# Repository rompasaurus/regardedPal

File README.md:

# Dilder

A Tamagotchi-inspired virtual pet built on a Raspberry Pi Pico W with an e-ink display, battery pack, and 3D-printed case — developed entirely in the open as a learning platform, blog series, and YouTube companion project.

The goal isn't just to build a thing — it's to show *how* the thing gets built, from the very first idea to a finished handheld device. Every prompt, every design decision, every dead end is documented so anyone can follow along, learn, and build their own.

---

## How It Started — Meet Jamal

<p align="center">
  
  <br />
  <em>Jamal. The plush octopus who started it all.</em>
</p>

This project didn't start with a schematic or a product spec. It started in a TEDi — a German dollar store — where my wife Emma and I found a giant plush octopus grinning up from a discount bin. We bought him on the spot, and on the walk home we started giving him a personality: laid-back, opinionated, a little sassy, suspiciously wise for a boneless creature. By the time we got home, he had a name — **Jamal** — and he'd claimed the armchair like he'd been paying rent.

The question asked itself: *what if we could actually bring him to life?* Not literally — but as a tiny digital companion. A pocket-sized octopus with moods, opinions, and an attitude problem, living on an e-ink screen and judging your life choices in ALL CAPS.

That's how Dilder was born. Not from an engineering roadmap, but from a stuffed animal and two people who couldn't stop anthropomorphizing it on a walk home.

---

## Enclosure — Rev 2 Mk2

The 3D-printed enclosure is a three-part design: base plate with solar panel recess, AAA battery cradle insert, and top cover with display window and joystick cutout. Designed in OpenSCAD (parametric source) and FreeCAD (visual PartDesign).

### Individual Parts

<p align="center">
  <em>Left: Base plate with cradle pocket, corner pillars, battery rail troughs, and USB-C cutout. Right: AAA battery cradle with dual bays, clip slots, and TP4056 indent.</em>
</p>

<p align="center">
  <em>Left: Top cover with display window, joystick hole, and bullnose edge. Right: Base plate bottom showing solar panel recess and wire holes.</em>
</p>

### Assembled

<p align="center">
  
  <br />
  <em>All three parts stacked in their mated positions.</em>
</p>

### Full Assembly with Electronics

The FreeCAD macro now imports the official Raspberry Pi Pico 2 STEP file (mechanically identical to the Pico 2 W) and adds procedural 2×20 pin headers. It also builds three more peripherals from datasheet dimensions — two AAA Li-Ion cells in the cradle bays, a TP4056 USB-C charge module in the connecting block indent, and a Waveshare 2.13" e-paper display in the top cover's screen inlay. The Pico is mounted upside-down with its component-side face flush against the cradle's mating plane, headers extending up into the PicoNest cavity.

<p align="center">
  
  <br />
  <em>Top cover rendered translucent so the Pico 2 W board, headers, and cradle are all visible.</em>
</p>

<p align="center">
  <em>Left: top cover hidden so the cradle and Pico are exposed. Right: cradle hidden so the Pico's seating on the base plate is visible — header pin tips reach the level where the cradle would clip in.</em>
</p>

See the [FreeCAD macro reference](website/docs/docs/hardware/freecad-mk2-macro.md) for a full walkthrough of how the macro is structured.

### Joystick Thumbpiece

A printable snap cap that fits over the K1-1506SN-01 5-way switch peg. Single disc, 11 mm OD (= cover hole − 1 mm) so it nests inside the cover's joystick cutout with 0.5 mm radial clearance for directional swing. Concave thumb dish on top, rectangular snap socket on the bottom centered on the actuator (the SW1 stick is offset +0.68 mm in Y from the cover hole on the production PCB layout — disc reads visually centered, socket lands on the peg). Built parametrically in `dilder_rev2_mk2.FCMacro` as a separate `Thumbpiece` Body — drop `thumb_sock_x/y` from 3.3 to ~3.15 in the spreadsheet to convert friction-fit to interference snap-fit.

<p align="center">
  
  <br />
  <em>Top-down view of the assembled prototype — display window on the left, joystick with the new thumbpiece on the right.</em>
</p>

<p align="center">
  <em>Left: joystick area in context. Right: thumbpiece nested in the cover cutout with the cover dialed to 85% transparency for clarity.</em>
</p>

See the [thumbpiece design write-up](website/docs/blog/posts/joystick-thumbpiece-snap-cap.md) for the geometry walkthrough — including the dish-vs-socket constraint that almost ruined the first cut.

---

## What This Project Is

- **A virtual pet device** — a pocket-sized, low-power companion with personality, needs, and interactions displayed on an e-ink screen
- **A build series** — a step-by-step guide covering hardware, software, 3D printing, and project planning
- **A transparency experiment** — the entire development process is captured in real time, including AI-assisted prompts, iteration, and mistakes

---

## Hardware

### Phase 1 — Pico W Prototype (current)

| Component | Details |
|-----------|---------|
| Board | Raspberry Pi Pico W (or Pico WH with pre-soldered headers) |
| Display | [Waveshare Pico-ePaper-2.13](https://www.waveshare.com/pico-epaper-2.13.htm) — 250x122px, black & white, SPI1, SSD1680 driver, Pico-native 40-pin plug-in module |
| Power | USB micro-B (development); battery TBD |
| Input | 5x 6x6mm tactile push buttons (3 nav + 2 action) via GPIO |

### Future — Pi Zero Upgrade

| Component | Details |
|-----------|---------|
| Board | Raspberry Pi Zero WH (W or 2 W, pre-soldered headers) |
| Power | LiPo battery + Adafruit PowerBoost 500C |
| Enclosure | 3D-printed case (STL files provided) |

> The Pico W is the starting platform — it's what we have on hand, it's cheap, and it's excellent for prototyping the display and input system. The Pi Zero upgrade comes later when we need Linux, networking features, or more compute.

---

## Phases

Each phase maps to a section of the blog/YouTube series and can be followed independently.

### Phase 0 — Project Planning & Documentation ✓

- [x] Create repository and project structure
- [x] Define project intent and scope
- [x] Begin prompt progression log ([PromptProgression.md](PromptProgression.md))
- [x] Outline full phase roadmap
- [x] Create pixel art concepts for e-ink display (octopus character with 16 emotional states)
- [x] Define enclosure concept and prototype dimensions

### Phase 1 — Hardware Selection & Setup (Pico W) ✓

- [x] Finalize component list with links/part numbers ([hardware-research.md](docs/hardware-research.md))
- [x] Set up Docker-based C SDK cross-compilation toolchain
- [x] Wire e-ink display to Pico W via jumper wires (SPI)
- [x] Flash and run "Hello, Dilder!" on the e-ink display — proof of life
- [x] Build DevTool GUI — display emulator, serial monitor, firmware flash, asset manager, GPIO reference, connection utility, documentation ([tools/devtool/](tools/devtool/))
- [x] Add Programs tab with animated octopus preview, firmware size estimation, and deploy
- [x] Build IMG-receiver firmware — stream images from PC to Pico display via USB serial ([dev-setup/img-receiver/](dev-setup/img-receiver/))
- [x] Build standalone deploy — runtime-rendered animation, runs without PC
- [ ] Wire and test button inputs (GPIO)
- [ ] Battery power prototype

### Phase 2 — Firmware Foundation (C on Pico W)
> *You are here*

- [x] Runtime rendering engine — draw octopus mathematically (no pre-baked frames)
- [x] Animation system — 4-frame mouth cycle with per-mood expression sequences
- [x] Body transform system — dx/dy offset, x_expand, per-row sine wobble
- [x] Custom body shapes for Fat (wider dome, thick tentacles) and Lazy (tentacles draped right)
- [x] 16 emotional states with unique eyes, pupils, eyebrows, eyelids, mouths, and body animations
- [x] 17 standalone firmware programs (16 emotions + mood selector with all 823 quotes)
- [x] Date/time clock header from RTC
- [x] C-faithful preview renderer for verifying firmware matches DevTool
- [x] Keyboard-to-Pico input mapping plan ([docs/keyboard-to-pico-input.md](docs/keyboard-to-pico-input.md))
- [x] Implement serial command input for interactive mood control
- [x] Wire and test GPIO joystick input (DollaTek 5-way, GP2–GP6)
- [x] Joystick Mood Selector firmware with on-screen input indicator
- [ ] **Custom PCB design (in progress)** — switched MCU from RP2040 to ESP32-S3-WROOM-1-N16R8 (WiFi+BLE, 16MB flash, 8MB PSRAM). 4-layer board (45x80mm, 30 components) in KiCad, ready for routing. Target fab: JLCPCB. Sensors: LIS2DH12TR (accelerometer), AHT20 (temperature/humidity), BH1750FVI-TR (ambient light) on shared I2C bus.
- [ ] Battery power (LiPo on VSYS) — InnCraft 1000mAh acquired
- [ ] Build game loop with state machine (idle, interact, sleep)

### Phase 3 — Pet Logic & Gameplay

- [ ] Define pet stats (hunger, happiness, energy, health, etc.)
- [ ] Implement stat decay over time
- [ ] Build interaction system — feed, play, sleep, clean
- [x] Pet mood / expressions based on emotional states (16 implemented)
- [x] Animation frames for e-ink (idle expressions, body movement per mood)
- [ ] Emotional state transitions triggered by interactions and stats
- [ ] Add death/game-over state and reset/new-pet flow

### Phase 4 — UI & Menus

- [ ] Design menu system for e-ink (optimized for minimal refreshes)
- [ ] Build status bar — icons for stats, clock, battery level
- [ ] Add screen transitions between menu, pet view, and interactions
- [ ] Implement settings screen (contrast, name pet, reset)

### Phase 5 — Pi Zero Migration

- [ ] Port MicroPython firmware to CPython on Pi Zero
- [ ] Set up headless Raspberry Pi OS
- [ ] Adapt display driver for Pi Zero SPI + Waveshare HAT
- [ ] Adapt input handler for Pi Zero GPIO
- [ ] Validate all Phase 2-4 functionality on Pi Zero

### Phase 6 — 3D-Printed Case & Power
> *In progress alongside Phase 2*

- [x] Design enclosure in OpenSCAD — parametric 3-part design (base plate, AAA cradle, top cover)
- [x] Account for display cutout, joystick access, USB-C charging port, solar panel recess
- [x] Translate to FreeCAD PartDesign — full parametric model with 90+ parameter spreadsheet
- [x] Battery cradle with clip slots for Swpeet AAA contact plates (parallel wiring)
- [x] Solar panel wire through-holes in base plate
- [x] Print prototypes and iterate on fit (Rev 2 Mk2 current)
- [ ] Implement battery power (dual 10440 or single 3000mAh LiPo via TP4056)
- [ ] Implement sleep/wake cycle to conserve battery
- [x] Publish STL/3MF files and build instructions ([hardware-design/freecad-mk2/](hardware-design/freecad-mk2/))

### Phase 7 — Extras & Community

- [ ] Add sound (piezo buzzer for beeps/alerts)
- [ ] Explore connectivity — Bluetooth/Wi-Fi pet interactions?
- [ ] Mini-games
- [ ] Seasonal/event-based pet outfits or moods
- [ ] Publish a "build your own" kit guide
- [ ] Community gallery — show off your Dilder

---

## Content & Documentation

| Resource | Description |
|----------|-------------|
| [PromptProgression.md](PromptProgression.md) | Every AI prompt used in development (104+), timestamped with token counts and file changes |
| [docs/hardware-research.md](docs/hardware-research.md) | Component research, materials list, GPIO pinout, and enclosure concepts |
| [Emotion States](https://dilder.dev/docs/software/emotion-states/) | All 16 emotional states with rendered previews and animation strips |
| [docs/keyboard-to-pico-input.md](docs/keyboard-to-pico-input.md) | Input mapping plan for interactive octopus control |
| [Blog](https://dilder.dev/blog/) | Build journal — 8 posts covering planning through body animations |
| YouTube (TBD) | Video walkthroughs for each phase |

---

## Follow Along

This project is built in the open. Star/watch this repo to follow progress. Each phase will have a corresponding blog post and video.

---

## License

TBD

---

*Built with patience, a Pico W, and an unreasonable fondness for a plush octopus named Jamal.*

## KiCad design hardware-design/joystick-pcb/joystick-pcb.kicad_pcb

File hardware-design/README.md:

# Build & Render Tool

Interactive CLI pipeline for rendering Dilder FreeCAD models into publication-quality PNGs.

## Quick Start

```bash
cd hardware-design
./build_and_render.sh
```

## What It Does

1. **Pick a model** — interactive menu lists all `.FCStd` files sorted by date (newest first)
2. **Choose what to render** — 19 options from full sets to individual components
3. **Set render style** — resolution, background, cover transparency
4. **Renders** — launches FreeCAD GUI, generates PNGs from the live 3D viewport
5. **Copies to website** — drops renders into `website/docs/assets/images/enclosure/`

## Menu Options

### Full Sets
| Option | Description | Images |
|--------|-------------|--------|
| 1 | Everything | 40+ |
| 2 | Assembly only | 10 |
| 3 | Exploded views | 3 |
| 4 | Component portraits | 14 |

### Individual Bodies
| Option | Description |
|--------|-------------|
| 5 | Base plate (iso + top + bottom + sensors) |
| 6 | AAA cradle (iso + top + bottom) |
| 7 | Top cover (transparent + opaque + bottom) |
| 8 | Thumbpiece |

### Peripherals
| Option | Description |
|--------|-------------|
| 9 | Joystick PCB (K1-1506SN-01 breakout) |
| 10 | Pico 2 W + headers |
| 11 | Piezo speaker (20 mm FT-20T) |
| 12 | IMU accelerometer (GY-6500) |
| 13 | TP4056 charger |
| 14 | Batteries + clips |
| 15 | E-ink display |
| 16 | Solar panel |

### Special
| Option | Description |
|--------|-------------|
| 17 | Detail close-ups (joystick, thumbpiece, sensors) |
| 18 | Animation frames (13-step assembly drop) |
| 19 | Custom combo (pick exactly which components) |

## Render Styles

- **Resolution:** 1920x1440 (default), 2560x1920, 1280x960, 960x720
- **Background:** Transparent (default), White, Black, Light gray
- **Cover transparency:** 40% (default), 0% (opaque), 70%, 85% (ghost)

## Animation

Option 18 generates frame-by-frame PNGs of components dropping into place with cosine ease-in-out. If `ffmpeg` is installed, assembles them into a GIF automatically.

```bash
# Manual GIF assembly if needed
ffmpeg -framerate 12 -i renders/anim/frame-%04d.png \
       -vf "scale=960:720" -loop 0 renders/assembly-animation.gif
```

## Flags

```bash
./build_and_render.sh --rebuild    # rebuild FCStd from macro before rendering
./build_and_render.sh --all        # (with animation) not needed — pick option 18 in menu
```

## Output

- `renders/var-*.png` — assembly views (hero, angles, exploded, etc.)
- `renders/comp-*.png` — isolated component portraits
- `renders/anim/frame-*.png` — animation frames
- Automatically copied to `website/docs/assets/images/enclosure/`

## Requirements

- FreeCAD (GUI version, not `freecadcmd` — needs the 3D viewport for `saveImage`)
- `ffmpeg` (optional, for GIF assembly)
- `identify` from ImageMagick (optional, for blank image detection)

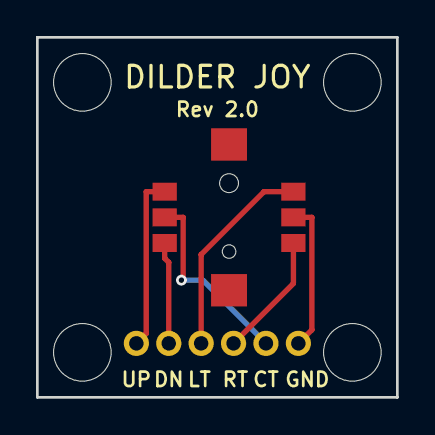
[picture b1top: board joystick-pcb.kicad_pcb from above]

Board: 2 copper layers, 20.0 x 20.0 mm, 6 parts (0 on the bottom side), 6 nets.

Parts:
H1, H2, H3, H4: M3; MountingHole_3.2mm_M3
J1: Wire_Pads; WirePads_1x06_P1.8mm
SW1: SKRHABE010

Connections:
GND: J1.6, SW1.5
JOY_CENTER: J1.5, SW1.2
JOY_DOWN: J1.2, SW1.3
JOY_LEFT: J1.3, SW1.4
JOY_RIGHT: J1.4, SW1.6
JOY_UP: J1.1, SW1.1

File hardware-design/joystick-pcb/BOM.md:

# Dilder Joystick Breakout PCB — Bill of Materials

## Rev 1.0 — 2026-04-25

---

### Components

| Ref | Qty | Description | Manufacturer | MPN | LCSC / JLCPCB | Package | Unit Price | Notes |
|-----|-----|-------------|-------------|-----|---------------|---------|------------|-------|
| SW1 | 1 | 5-direction SMD navigation switch | Alps Alpine | SKRHABE010 | C139794 | SMD-8P, 7.5x7.5mm | $0.50 (qty 100) | Primary joystick input |
| J1 | 1 | 1x6 through-hole wire pads | — | — | — | 2.0mm pitch, PTH | $0.00 | Bare pads for hand-soldered wires |
| H1-H4 | 4 | M3 mounting hole | — | — | — | 3.2mm drill, NPTH | $0.00 | Board-only (no BOM part) |

### PCB Fabrication

| Parameter | Value |
|-----------|-------|
| Board size | 20 x 20 mm |
| Layers | 2 (F.Cu + B.Cu) |
| Thickness | 1.0 mm |
| Copper weight | 1 oz |
| Surface finish | HASL (lead-free) |
| Solder mask | Green (default) |
| Silkscreen | White |
| Min trace width | 0.3 mm |
| Min drill | 1.0 mm (wire pads) |
| NPTH drills | 3.2 mm x4 (M3 mounting) |

### JLCPCB Order Notes

- **PCB only (no assembly):** Order 5-10 boards at ~$2 for the lot
- **With PCBA (recommended):** Use Economic PCBA, single-side SMT
  - SKRHABE010 is an **Extended Part** — $3 setup fee per unique extended part
  - Assembly requires fixture (noted on JLCPCB part page)
  - Upload BOM CSV + CPL (pick-and-place) file
  - J1 wire pads are hand-soldered after assembly — exclude from PCBA BOM

### Alternative Components (drop-in replacements)

| MPN | Manufacturer | LCSC | Price | Stock | Notes |
|-----|-------------|------|-------|-------|-------|
| SKRHABE010 | Alps Alpine | C139794 | $0.50 | ~3,325 | **Primary choice** |
| TM-4175-B-A | XKB Connection | C465995 | $0.73 | ~748 | Same 8-pin footprint, compatible |
| SKRHADE010 | Alps Alpine | C202415 | $0.85 | ~742 | Alps variant, same footprint |

### Wiring to ESP32-S3 (Olimex DevKit-Lipo)

| J1 Pin | Signal | Wire Color (suggested) | ESP32-S3 GPIO |
|--------|--------|----------------------|---------------|
| 1 | JOY_UP | White | GPIO4 |
| 2 | JOY_DOWN | Yellow | GPIO5 |
| 3 | JOY_LEFT | Orange | GPIO6 |
| 4 | JOY_RIGHT | Green | GPIO7 |
| 5 | JOY_CENTER | Blue | GPIO8 |
| 6 | GND | Black | GND |

### Total Cost Estimate (5 boards + assembly)

| Item | Cost |
|------|------|
| PCB fabrication (5 pcs) | ~$2.00 |
| SKRHABE010 x5 | ~$2.50 |
| Extended part fee | $3.00 |
| SMT assembly (5 pcs) | ~$5.00 |
| Shipping (economy) | ~$3.00 |
| **Total** | **~$15.50** |

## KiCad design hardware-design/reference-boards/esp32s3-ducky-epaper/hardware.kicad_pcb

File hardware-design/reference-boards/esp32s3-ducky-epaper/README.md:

# Ducky Board - Esp32-S3 with1.52-inch e-paper display

This project is a custom-designed breakout board for the ESP32-S3 chip, created using KiCad 9. The board features an e-ink display (gdem0154z91 from good display) native USB-C programming support, and includes an integrated Li-Ion battery charger,

## Hardware

- **Features**

-ESP32-S3 Microcontroller

-3 color epaper display (gdem0154z91)

-USB-C Port

  Used for both power input and firmware flashing

-Li-Ion Battery Charging Circuit

  Integrated charger IC with status indicators

  Supports single-cell Li-Ion/LiPo batteries

-Compact Breakout Form Factor

  All key GPIOs broken out

## Design Details

-Designed entirely in KiCad 9

-Includes schematics, PCB layout files, and Gerber files

-Part selection is optimized for manufacturing and re-usability for DIY projects

## License

See the [LICENSE](LICENSE) file for details.

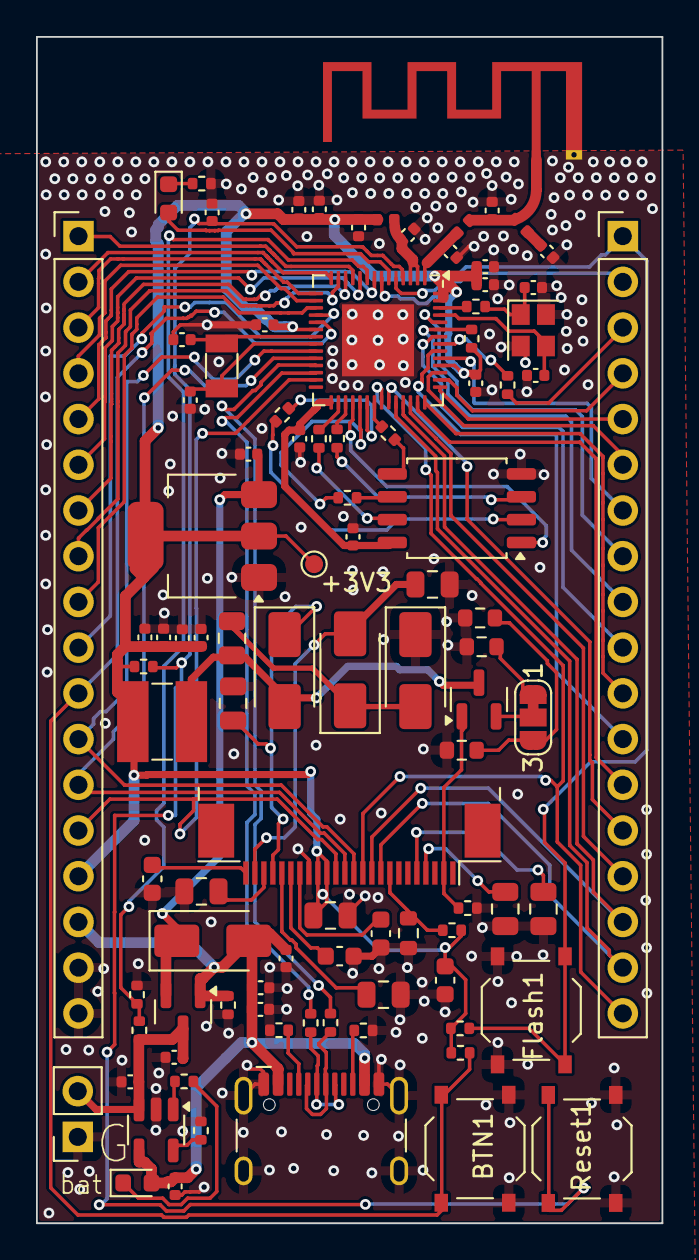
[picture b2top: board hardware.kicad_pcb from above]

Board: 2 copper layers, 34.8 x 65.9 mm, 97 parts (0 on the bottom side), 86 nets.

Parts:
+3V3: +3V3; TestPoint_Pad_D1.0mm
AE1: Antenna; Texas_SWRA117D_2.4GHz_Left
BTN1: BTN; SW_Push_1P1T_XKB_TS-1187A
C2, C3, C6, C7, C8, C16, C17, C20, C25, C36: 10uF; C_0402_1005Metric
C4, C33, C37, C38: 12pF; C_0402_1005Metric
C10, C11, C15, C18, C19, C22, C32, C35: 0.1uF; C_0402_1005Metric
C13, C26, C39: 1uF; C_0402_1005Metric
C14: DNP; C_0402_1005Metric
C29, C30, C34, C41: 1uF; C_0603_1608Metric
C31: 15pF; C_0402_1005Metric
C40: 10nF; C_0402_1005Metric
C48, C49, C50, C51, C52, C53, C54, C55: 4.7uF; C_0805_2012Metric
D1, D3: LED; LED_0603_1608Metric
D4, D5, D6, D7: SS14; D_SMA
DNP1: 15pF; C_0402_1005Metric
Flash1: Flash; SW_Push_1P1T_XKB_TS-1187A
J1: USB_C_Receptacle_USB2.0_14P; USB_C_Receptacle_HCTL_HC-TYPE-C-16P-01A
J2: Conn_01x02_Pin; PinSocket_1x02_P2.54mm_Vertical
J3, J5: Conn_01x18_Pin; PinHeader_1x18_P2.54mm_Vertical
JP1: SolderJumper_3_Bridged12; SolderJumper-3_P1.3mm_Bridged12_RoundedPad1.0x1.5mm_NumberL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
L3: 2nH; L_0402_1005Metric
L4: 10uH; L_Ferrocore_DLG-0403
L5: DNP; L_0402_1005Metric
L6: 4.7nH; L_0402_1005Metric
P4: AFC07-S24FCC-00; Jushuo_AFC07-S24FCA-00_1x24-1MP_P0.50_Horizontal
Q1: AO3401A; SOT-23
Q3: AO3400A; SOT-23
R1: 2K; R_0402_1005Metric
R2, R18: 33R; R_0402_1005Metric
R3, R4, R21, R22, R33, R35: 10K; R_0402_1005Metric
R12, R19: 200K; R_0402_1005Metric
R14, R17: 5.1K; R_0402_1005Metric
R20: 100K; R_0402_1005Metric
R23, R26, R27, R28, R29, R30: 0R; R_0402_1005Metric
R24, R25: 470R; R_0402_1005Metric
R31: DNP; R_0402_1005Metric
R34, R37: 2.2R; R_0603_1608Metric
R36, R38: 1R; R_0603_1608Metric
Reset1: Reset; SW_Push_1P1T_XKB_TS-1187A
U1: ESP32-S3; QFN-56-1EP_7x7mm_P0.4mm_EP4x4mm
U2: W25Q128JVS; SOIC-8_5.3x5.3mm_P1.27mm
U3: MCP73831-2-OT; SOT-23-5
U4: AMS1117-3.3; SOT-223-3_TabPin2
Y1: 32.768 kHz; Crystal_SMD_3215-2Pin_3.2x1.5mm
Y2: 40MHz(10ppm); Crystal_SMD_2520-4Pin_2.5x2.0mm

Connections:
5V: C6.1, C16.1, C22.1, C36.1, D1.2 (A), D4.2 (A), J1.A4 (VBUS), J1.A9 (VBUS), J1.B4 (VBUS), J1.B9 (VBUS), J3.16, Q1.1 (G), R20.2, U3.4 (V_{DD})
EN: C15.1, R22.1, Reset1.2, U1.4 (CHIP_PU)
GDR: P4.2 (GDR), Q3.1 (G), R35.2
GND: AE1.2 (PCB_Trace), BTN1.1, C2.2, C3.2, C4.2, C6.2, C7.2, C8.2, C10.2, C11.2, C13.2, C14.2, C15.2, C16.2, C17.2, C18.2, C19.2, C20.2, C22.2, C25.2, C26.2, C29.2, C30.2, C31.2, C32.2, C33.1, C34.2, C35.2, C36.2, C37.2, C38.2, C39.2, C40.2, C41.2, C48.2, C50.2, C51.2, C52.2, C53.2, C54.2, C55.2, D5.1 (K), DNP1.2, Flash1.1, J1.A1 (GND), J1.A12 (GND), J1.B1 (GND), J1.B12 (GND), J1.S1 (SHIELD), J2.1, J3.17, J3.18, P4.17 (VSS), R1.1, R14.1, R17.1, R19.2, R20.1, R25.2, R34.1, R35.1, R36.1, R37.1, R38.1, Reset1.1, U1.57 (GND), U2.4 (GND), U3.2 (V_{SS}), U4.1 (GND), Y2.2, Y2.4
IO0: Flash1.2, J5.1, R21.2, U1.5 (GPIO0)
IO1: D3.2 (A), U1.6 (GPIO1)
IO2: J5.2, U1.7 (GPIO2)
IO3: J3.5, U1.8 (GPIO3)
IO4/BAT: R12.2, R19.1, U1.9 (GPIO4)
IO5: J3.6, U1.10 (GPIO5)
IO6: J3.1, U1.11 (GPIO6)
IO7: J3.7, U1.12 (GPIO7)
IO8: J3.8, U1.13 (GPIO8)
IO9: J3.2, U1.14 (GPIO9)
IO10: J3.3, U1.15 (GPIO10)
IO11: J3.4, U1.16 (GPIO11)
IO12: J3.9, U1.17 (GPIO12)
IO13: J3.10, U1.18 (GPIO13)
IO14: BTN1.2, J3.11, R4.2, U1.19 (GPIO14)
IO17: J3.12, P4.12 (~CS), U1.23 (GPIO17)
IO18: J3.13, P4.13 (SCL), U1.24 (GPIO18)
IO21: J3.14, P4.14 (SDA), U1.27 (GPIO21)
IO33: J5.17, P4.9 (BUSY), U1.38 (GPIO33)
IO34: J5.16, P4.10 (RESET), U1.39 (GPIO34)
IO35: J5.15, U1.40 (GPIO35)
IO36: J5.13, U1.41 (GPIO36)
IO37: J5.11, U1.42 (GPIO37)
IO38: J5.5, U1.43 (GPIO38)
IO39: J5.4, U1.44 (MTCK)
IO40: J5.6, U1.45 (MTDO)
IO41: J5.7, U1.47 (MTDI)
IO42: J5.12, U1.48 (MTMS)
IO45: J5.9, R31.1, U1.51 (GPIO45)
IO46: J5.8, U1.52 (GPIO46)
IO47: J5.14, U1.37 (SPICLK_P)
IO48: J5.18, P4.11 (DATA/~CMD), U1.36 (SPICLK_N)
unnamed: AE1.1 (FEED), C31.1, L5.2, L6.2
unnamed: C4.1, R23.1, Y2.1
unnamed: C14.1, L5.1
unnamed: C19.1, L3.2, U1.2 (VDD3P3), U1.3 (VDD3P3)
unnamed: C52.1, P4.4 (NC)
unnamed: D1.1 (K), R3.2
unnamed: D3.1 (K), R25.1
unnamed: C49.1, D5.2 (A), D6.1 (K)
unnamed: C49.2, D7.2 (A), L4.2, Q3.3 (D)
unnamed: J1.A5 (CC1), R14.2
unnamed: J1.B5 (CC2), R17.2
unnamed: JP1.1 (A), R34.2
unnamed: JP1.3 (B), R36.2, R38.2
unnamed: JP1.2 (C), Q3.2 (S)
unnamed: P4.8 (BS1), R33.1, R37.2
unnamed: C30.1, P4.18 (VDD)
unnamed: C29.1, P4.19 (VPP)
unnamed: C55.1, P4.20 (VSH1)
unnamed: C53.1, P4.5 (VSH2)
unnamed: C54.1, P4.22 (VSL)
unnamed: DNP1.1, L6.1, U1.1 (LNA_IN)
unnamed: R28.1, U1.33 (SPICLK)
unnamed: R26.1, U1.35 (SPID)
unnamed: R30.1, U1.30 (SPIHD)
unnamed: R27.1, U1.34 (SPIQ)
unnamed: R29.1, U1.31 (SPIWP)
unnamed: R24.1, U1.49 (U0TXD)
unnamed: C33.2, U1.53 (XTAL_N), Y2.3
unnamed: R23.2, U1.54 (XTAL_P)
unnamed: R1.2, U3.5 (PROG)
unnamed: R3.1, U3.1 (STAT)
PREVGH: C50.1, D7.1 (K), P4.21 (VGH)
PREVGL: C48.1, D6.2 (A), P4.23 (VGL)
RX: J5.10, U1.50 (U0RXD)
SPICS0: U1.32 (SPICS0), U2.1 (~CS)
SPID: R26.2, U2.5 (DI/IO_{0})
SPIHD: R30.2, U2.7 (~HOLD/~RESET/IO_{3})
SPIQ: R27.2, U2.2 (DO/IO_{1})
SPISCK: R28.2, U2.6 (CLK)
SPIWP: R29.2, U2.3 (~WP/IO_{2})
TX: J5.3, R24.2
USB_D+: J1.A6 (D+), J1.B6 (D+), R18.1, R18.2, U1.26 (GPIO20/USB_D+)
USB_D-: J1.A7 (D-), J1.B7 (D-), R2.1, R2.2, U1.25 (GPIO19/USB_D-)
VBAT: C2.1, C8.1, J2.2, Q1.3 (D), R12.1, U3.3 (V_{BAT})
VCOM: C34.1, P4.24 (VCOM)
VDD_CPU: +3V3.1, C3.1, C10.1, C11.1, C17.1, C18.1, C20.1, C25.1, C26.1, C35.1, C39.1, C40.1, C41.1, C51.1, J3.15, L3.1, L4.1, P4.15 (VDDIO), P4.16 (VCI), R4.1, R21.1, R22.2, R31.2, R33.2, U1.20 (VDD3P3_RTC), U1.46 (VDD3P3_CPU), U1.55 (VDDA), U1.56 (VDDA), U4.2 (VO)
VDD_SPI: C13.1, C32.1, U1.29 (VDD_SPI), U2.8 (VCC)
VSYS: C7.1, D4.1 (K), Q1.2 (S), U4.3 (VI)
XTAL32N: C37.1, U1.22 (XTAL_32K_N), Y1.1
XTAL32P: C38.1, U1.21 (XTAL_32K_P), Y1.2

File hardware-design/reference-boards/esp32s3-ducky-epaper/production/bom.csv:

Designator,Footprint,Quantity,Value,LCSC Part #
+3V3,TestPoint_Pad_D1.0mm,1,+3V3,
AE1,Texas_SWRA117D_2.4GHz_Left,1,Antenna,
BTN1,SW_Push_1P1T_XKB_TS-1187A,1,BTN,C318884
"C10, C11, C15, C18, C19, C22, C32, C35",0402,8,0.1uF,C1525
"C13, C26, C39",0402,3,1uF,C52923
"C16, C17, C2, C20, C25, C3, C36, C6, C7, C8",0402,10,10uF,C15525
"C29, C30, C34, C41",0603,4,1uF,C15849
"C31, DNP1",0402,2,15pF,C1548
"C33, C37, C38, C4",0402,4,12pF,C1547
C40,0402,1,10nF,C15195
"C48, C49, C50, C51, C52, C53, C54, C55",0805,8,4.7uF,C1779
"D1, D3",0603,2,LED,C2286
"D4, D5, D6, D7",D_SMA,4,SS14,C2480
FLASH1,SW_Push_1P1T_XKB_TS-1187A,1,Flash,C318884
J1,USB_C_Receptacle_HCTL_HC-TYPE-C-16P-01A,1,USB_C_Receptacle_USB2.0_14P,C19274016
J2,PinSocket_1x02_P2.54mm_Vertical,1,Conn_01x02_Pin,
"J3, J5",PinHeader_1x18_P2.54mm_Vertical,2,Conn_01x18_Pin,
L3,0402,1,2nH,C77103
L4,L_Ferrocore_DLG-0403,1,10uH,C2929419
L6,0402,1,4.7nH,C13595
P4,Jushuo_AFC07-S24FCA-00_1x24-1MP_P0.50_Horizontal,1,AFC07-S24FCC-00,C11057
Q1,SOT-23,1,AO3401A,C15127
Q3,SOT-23,1,AO3400A,C20917
R1,0402,1,2K,C4109
"R12, R19",0402,2,200K,C25764
"R14, R17",0402,2,5.1K,C25905
"R18, R2",0402,2,33R,C25105
R20,0402,1,100K,C25741
"R21, R22, R3, R33, R35, R4",0402,6,10K,C25744
"R23, R26, R27, R28, R29, R30",0402,6,0R,C17168
"R24, R25",0402,2,470R,C25117
"R34, R37",0603,2,2.2R,C22939
"R36, R38",0603,2,1R,C22936
RESET1,SW_Push_1P1T_XKB_TS-1187A,1,Reset,C318884
U1,QFN-56-1EP_7x7mm_P0.4mm_EP4x4mm,1,ESP32-S3,C2913194
U2,SOIC-8_5.3x5.3mm_P1.27mm,1,W25Q128JVS,C97521
U3,SOT-23-5,1,MCP73831-2-OT,C7472804
U4,SOT-223-3_TabPin2,1,AMS1117-3.3,C6186
Y1,Crystal_SMD_3215-2Pin_3.2x1.5mm,1,32.768 kHz,C32346
Y2,Crystal_SMD_2520-4Pin_2.5x2.0mm,1,40MHz(10ppm),C5261125

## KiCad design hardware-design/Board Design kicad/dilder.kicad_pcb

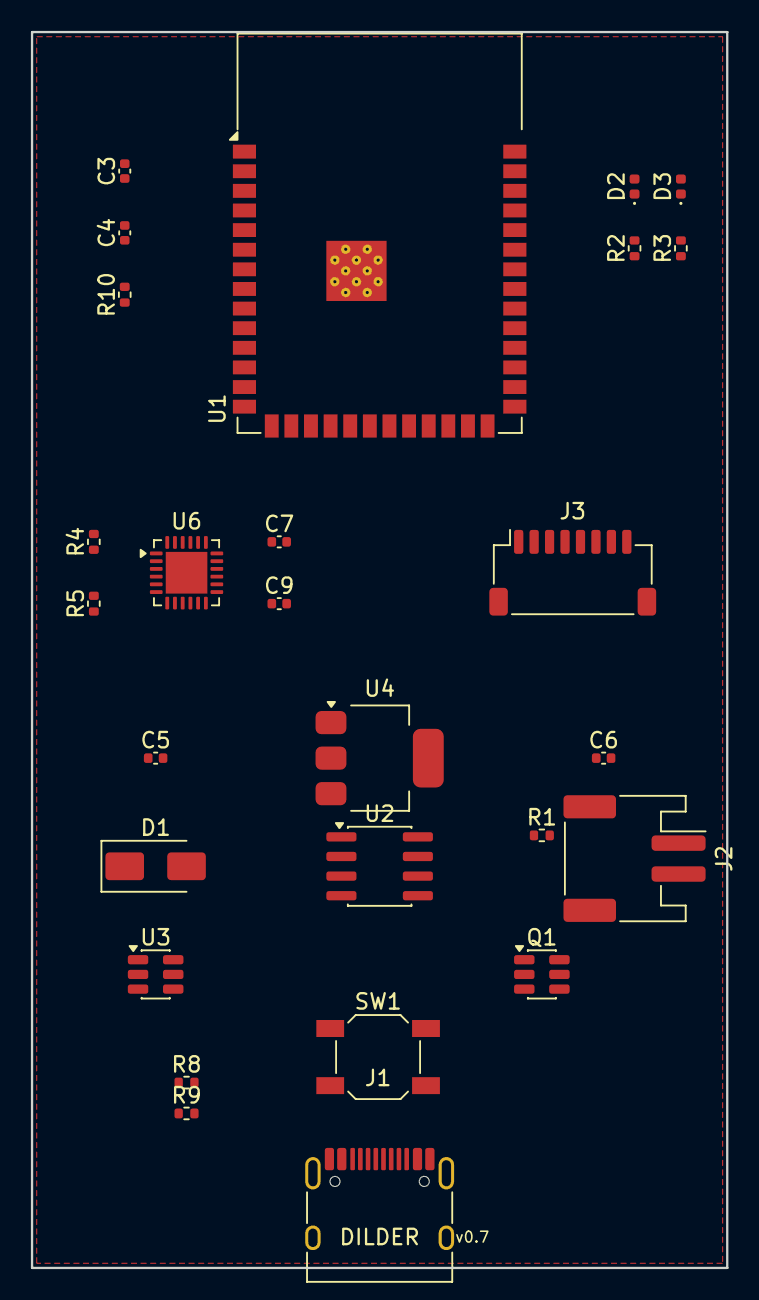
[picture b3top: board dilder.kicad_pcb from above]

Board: 4 copper layers, 45.0 x 80.0 mm, 27 parts (0 on the bottom side), 29 nets, no tracks yet.

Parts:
C3, C7, C9: 100nF; C_0402_1005Metric
C4, C5, C6: 10uF; C_0402_1005Metric
D1: SS34; D_SMA
D2: RED; LED_0402_1005Metric
D3: GREEN; LED_0402_1005Metric
J1: USB-C; USB_C_Receptacle_HRO_TYPE-C-31-M-12
J2: BAT; JST_PH_S2B-PH-SM4-TB_1x02-1MP_P2.00mm_Horizontal
J3: ePaper; JST_SH_SM08B-SRSS-TB_1x08-1MP_P1.00mm_Horizontal
Q1: FS8205A; SOT-23-6
R1: 1.2k; R_0402_1005Metric
R2, R3: 1k; R_0402_1005Metric
R4, R5, R10: 10k; R_0402_1005Metric
R8, R9: 5.1k; R_0402_1005Metric
SW1: 5-Way; SW_SPST_SKQG_WithStem
U1: ESP32-S3-N16R8; ESP32-S3-WROOM-1
U2: TP4056; SOIC-8_3.9x4.9mm_P1.27mm
U3: DW01A; SOT-23-6
U4: AMS1117-3.3; SOT-223-3_TabPin2
U6: MPU-6050; QFN-24-1EP_4x4mm_P0.5mm_EP2.7x2.7mm

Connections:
3V3: C3.1, C4.1, C6.1, C7.1, J3.1, R2.1, R3.1, R4.1, R5.1, R10.1, U1.2, U2.4, U4.2, U6.1, U6.13
BAT_PLUS: J2.1, Q1.6
CC1: J1.A5, R8.1
CC2: J1.B5, R9.1
CHRG_LED: D2.1, R2.2
CHRG_OUT: D2.2, U2.7
CS_DRAIN: Q1.3, Q1.4, U3.2
EN: R10.2, U1.3
EPD_BUSY: J3.8, U1.20
EPD_CLK: J3.4, U1.15
EPD_CS: J3.5, U1.19
EPD_DC: J3.6, U1.17
EPD_MOSI: J3.3, U1.16
EPD_RST: J3.7, U1.18
GND: C3.2, C4.2, C5.2, C6.2, C7.2, C9.2, J1.A1, J1.A12, J1.B1, J1.B12, J2.2, J3.2, Q1.1, R1.2, R8.2, R9.2, SW1.1, U1.1, U1.31, U1.32, U1.40, U1.41, U2.1, U2.5, U3.6, U4.1, U6.8, U6.9, U6.11, U6.18
I2C_SCL: R5.2, U1.10, U6.23
I2C_SDA: R4.2, U1.9, U6.24
JOY_CENTER: SW1.2, U1.8
OC: Q1.5, U3.3
OD: Q1.2, U3.1
PROG: R1.1, U2.2
REGOUT: C9.1, U6.10
STDBY_LED: D3.1, R3.2
STDBY_OUT: D3.2, U2.6
USB_DM: J1.A7, J1.B7, U1.13
USB_DP: J1.A6, J1.B6, U1.14
VBAT: C5.1, U2.3, U3.4, U3.5, U4.3
VBUS: D1.1, J1.A4, J1.B4
VBUS_CHG: D1.2, U2.8

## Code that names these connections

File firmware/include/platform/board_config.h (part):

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 *  (which would make switching boards a nightmare), we define them
 *  all HERE using #define macros with consistent names.
 *
 *  The rest of the code just uses PIN_EPD_CLK everywhere.  This file
 *  ensures PIN_EPD_CLK expands to the right number for whichever board
 *  we're building for.
 *
 *  Think of it like a wiring diagram in code form: "On this board,
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 *
 * Each #define creates a macro that the preprocessor replaces
 * throughout the code.  For example, everywhere the code says
 * PIN_EPD_CLK, the preprocessor substitutes the number 10.
 *
 * The comments show: GPIO number, SPI function, physical pin on
 * the Pico W board header.  "GP10" means GPIO pin 10, which is
 * physical pin 14 on the board's 40-pin header.
 */
#define PIN_EPD_CLK         10   /* GP10  SPI1 SCK   pin 14 */
#define PIN_EPD_DIN         11   /* GP11  SPI1 TX    pin 15 */
#define PIN_EPD_CS           9   /* GP9              pin 12 */
#define PIN_EPD_DC           8   /* GP8              pin 11 */
#define PIN_EPD_RST         12   /* GP12             pin 16 */
#define PIN_EPD_BUSY        13   /* GP13             pin 17 */

/* 5-way joystick / buttons (K1-1506SN-01 breakout PCB from JLCPCB)
 *
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#define BOARD_NAME          "Pico 2 W"

/* e-Paper display — SPI1 (same pins as Pico W) */
#define PIN_EPD_CLK         10   /* GP10  SPI1 SCK   pin 14 */
#define PIN_EPD_DIN         11   /* GP11  SPI1 TX    pin 15 */
#define PIN_EPD_CS           9   /* GP9              pin 12 */
#define PIN_EPD_DC           8   /* GP8              pin 11 */
#define PIN_EPD_RST         12   /* GP12             pin 16 */
#define PIN_EPD_BUSY        13   /* GP13             pin 17 */

/* 5-way joystick / buttons (same pins as Pico W — K1-1506SN-01 breakout PCB) */
#define PIN_BTN_LEFT         2   /* GP2   pin 4  — PCB pad "L"  */
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 * pins.  The EXT1-XX comments refer to pin numbers on the pUEXT
 * connector (not the GPIO numbers — those are the #define values).
 *
 * Note: GPIO10 has a 10k pull-up resistor on the board, which is
 * fine for a chip-select line (CS idles HIGH anyway).
 */
#define PIN_EPD_CLK         12   /* GPIO12  FSPI CLK   EXT1-18 */
#define PIN_EPD_DIN         11   /* GPIO11  FSPI MOSI  EXT1-17 */
#define PIN_EPD_CS          10   /* GPIO10  FSPI CS    EXT1-16 (10k pull-up) */
#define PIN_EPD_DC           9   /* GPIO9             EXT1-15 */
#define PIN_EPD_RST          3   /* GPIO3  (strapping, safe after boot) EXT1-13 */
#define PIN_EPD_BUSY         8   /* GPIO8             EXT1-12 */

/* 5-way joystick — spread across EXT1 and EXT2 connectors */
#define PIN_BTN_UP           4   /* GPIO4   EXT1-4  */
#define PIN_BTN_DOWN         7   /* GPIO7   EXT1-7  */
#define PIN_BTN_LEFT         1   /* GPIO1   EXT2-4  */
#define PIN_BTN_RIGHT        2   /* GPIO2   EXT2-5  */
#define PIN_BTN_CENTER      15   /* GPIO15  EXT1-8  */

/*
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 * requires.  They're defined here for future use (e.g., temperature
 * sensor, light sensor) but nothing uses them yet.
 */
#define PIN_I2C_SDA         48   /* GPIO48  EXT2-16 */
#define PIN_I2C_SCL         47   /* GPIO47  EXT2-17 */

/* Flash size — the Olimex ESP32-S3 board has 8 MB of flash.
 * That's 4x more than the Pico W, giving us plenty of room
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 * libraries to simulate the hardware.  So these pin numbers are
 * never used for real I/O; they just keep the compiler happy.
 */
#define PIN_EPD_CLK          0
#define PIN_EPD_DIN          0
#define PIN_EPD_CS           0
#define PIN_EPD_DC           0
#define PIN_EPD_RST          0
#define PIN_EPD_BUSY         0

#define PIN_BTN_UP           0
#define PIN_BTN_DOWN         0
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
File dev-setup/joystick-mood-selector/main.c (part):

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 * Serial input is still supported as a fallback.
 *
 * Display wiring (Pico-ePaper-2.13):
 *   VSYS -> VSYS     pin 39    GND  -> GND      pin 38
 *   DIN  -> GP11     pin 15    CLK  -> GP10     pin 14
 *   CS   -> GP9      pin 12    DC   -> GP8      pin 11
 *   RST  -> GP12     pin 16    BUSY -> GP13     pin 17
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/* Joystick GPIO pins (active LOW with internal pull-ups)
 * K1-1506SN-01 breakout PCB — Com=GND(pin3), L=GP2, D=GP3, UP=GP4, R=GP5, C=GP6
 */
#define JOY_LEFT   2
#define JOY_DOWN   3
#define JOY_UP     4
#define JOY_RIGHT  5
#define JOY_CENTER 6

/* Debounce: minimum ms between joystick reads */
#define DEBOUNCE_MS 200
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/* ─── Joystick GPIO initialization ─── */

static void joystick_init(void) {
    const uint pins[] = {JOY_UP, JOY_DOWN, JOY_LEFT, JOY_RIGHT, JOY_CENTER};
    for (int i = 0; i < 5; i++) {
        gpio_init(pins[i]);
        gpio_set_dir(pins[i], GPIO_IN);
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    for (int t = 0; t < 3; t++) {
        printf("  Read %d: L=%d D=%d U=%d R=%d C=%d  (1=HIGH/released, 0=LOW/pressed)\n",
               t + 1,
               gpio_get(JOY_LEFT), gpio_get(JOY_DOWN), gpio_get(JOY_UP),
               gpio_get(JOY_RIGHT), gpio_get(JOY_CENTER));
        sleep_ms(500);
    }
    printf("--- End GPIO Diagnostic ---\n\n");
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            /* ── GPIO raw state dump every 2s (unconditional) ── */
            if (now - last_gpio_dump >= 2000) {
                printf("  [GPIO] L(GP%d)=%d D(GP%d)=%d U(GP%d)=%d R(GP%d)=%d C(GP%d)=%d\n",
                       JOY_LEFT,  gpio_get(JOY_LEFT),
                       JOY_DOWN,  gpio_get(JOY_DOWN),
                       JOY_UP,    gpio_get(JOY_UP),
                       JOY_RIGHT, gpio_get(JOY_RIGHT),
                       JOY_CENTER,gpio_get(JOY_CENTER));
                last_gpio_dump = now;
            }

            /* ── Joystick GPIO polling (active LOW, debounced) ── */
            if (now - last_joy_time >= DEBOUNCE_MS) {
                if (gpio_get(JOY_LEFT) == 0) {
                    current_mood = (current_mood == 0) ? MOOD_COUNT - 1 : current_mood - 1;
                    snprintf(last_input, sizeof(last_input), "LEFT");
                    last_joy_time = now;
                    printf("  [JOY] LEFT  -> %s\n", mood_names[current_mood]);
                    mood_changed = true;
                    input_received = true;
                } else if (gpio_get(JOY_RIGHT) == 0) {
                    current_mood = (current_mood + 1) % MOOD_COUNT;
                    snprintf(last_input, sizeof(last_input), "RIGHT");
                    last_joy_time = now;
                    printf("  [JOY] RIGHT -> %s\n", mood_names[current_mood]);
                    mood_changed = true;
                    input_received = true;
                } else if (gpio_get(JOY_UP) == 0) {
                    current_mood = rng_next() % MOOD_COUNT;
                    snprintf(last_input, sizeof(last_input), "UP");
                    last_joy_time = now;
                    printf("  [JOY] UP    -> %s (random)\n", mood_names[current_mood]);
                    mood_changed = true;
                    input_received = true;
                } else if (gpio_get(JOY_DOWN) == 0) {
                    qi = pick_quote_for_mood(current_mood);
                    snprintf(last_input, sizeof(last_input), "DOWN");
                    last_joy_time = now;
                    printf("  [JOY] DOWN  -> new quote\n");
                    mood_changed = true;
                    input_received = true;
                } else if (gpio_get(JOY_CENTER) == 0) {
                    current_mood = MOOD_NORMAL;
                    snprintf(last_input, sizeof(last_input), "CTR");
                    last_joy_time = now;
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
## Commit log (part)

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2026-04-09 Deployed e358a1f with MkDocs version: 1.6.1
2026-04-09 Trigger first GitHub Pages deployment
2026-04-09 Deployed 18c8876 with MkDocs version: 1.6.1
2026-04-09 Deployed 0af7962 with MkDocs version: 1.6.1
2026-04-09 Create CNAME
2026-04-09 Deployed 61525d6 with MkDocs version: 1.6.1
2026-04-12 Deployed c5c295d with MkDocs version: 1.6.1
2026-04-12 Deployed 75fb79a with MkDocs version: 1.6.1
2026-04-12 Deployed 7e06495 with MkDocs version: 1.6.1
2026-04-12 Deployed a6f174c with MkDocs version: 1.6.1
2026-04-12 Deployed ec59806 with MkDocs version: 1.6.1
2026-04-12 Deployed deb3291 with MkDocs version: 1.6.1
2026-04-12 Deployed dd837c7 with MkDocs version: 1.6.1
2026-04-13 Deployed b0fd97a with MkDocs version: 1.6.1
2026-04-13 fixed lining in drawing
2026-04-14 Deployed b6ec18d with MkDocs version: 1.6.1
2026-04-14 Deployed d8ff202 with MkDocs version: 1.6.1
2026-04-14 Deployed 69ad9a9 with MkDocs version: 1.6.1
2026-04-14 Deployed 55189fd with MkDocs version: 1.6.1
2026-04-15 Deployed e11a78d with MkDocs version: 1.6.1
2026-04-15 Deployed d12d85f with MkDocs version: 1.6.1
2026-04-15 Deployed dbc82c1 with MkDocs version: 1.6.1
2026-04-15 Deployed dd3f5b3 with MkDocs version: 1.6.1
2026-04-15 Deployed 9303d83 with MkDocs version: 1.6.1
2026-04-15 added lingering board designs
2026-04-16 Deployed f07ae18 with MkDocs version: 1.6.1
2026-04-16 Deployed feec5ba with MkDocs version: 1.6.1
2026-04-17 Deployed 0a64ad8 with MkDocs version: 1.6.1
2026-04-17 Deployed 76f3079 with MkDocs version: 1.6.1
2026-04-21 created v1 proto for the case batt and esp32
2026-04-22 Deployed 3290bc8 with MkDocs version: 1.6.1
2026-04-22 Deployed 941a610 with MkDocs version: 1.6.1
2026-04-22 Deployed 7b4fe5e with MkDocs version: 1.6.1
2026-04-22 Deployed f535843 with MkDocs version: 1.6.1
2026-04-22 more ptints gened
2026-04-22 Deployed 762625a with MkDocs version: 1.6.1
2026-04-22 Deployed 5e1ee71 with MkDocs version: 1.6.1
2026-04-23 Deployed 95142b7 with MkDocs version: 1.6.1
2026-04-23 Deployed 575dea2 with MkDocs version: 1.6.1
2026-04-23 re-orged models
2026-04-23 Deployed 1b69cce with MkDocs version: 1.6.1
2026-04-23 Deployed 05a261b with MkDocs version: 1.6.1
2026-04-24 Deployed 2560376 with MkDocs version: 1.6.1
2026-04-24 Deployed 9dd9b58 with MkDocs version: 1.6.1
2026-04-25 Deployed d5ba2d8 with MkDocs version: 1.6.1
2026-04-25 deleted heic files that have been converted to jpeg
2026-04-25 Deployed 5739127 with MkDocs version: 1.6.1
2026-04-25 Deployed c039cf2 with MkDocs version: 1.6.1
2026-04-25 Deployed 0204688 with MkDocs version: 1.6.1
2026-04-26 slight adjustments to pcb board for legibility
2026-04-26 adde some supports to model and preset for todays prints
2026-04-26 add preset for front plate lower the radius thickened the front plane
2026-04-26 Deployed e86efd7 with MkDocs version: 1.6.1
2026-04-26 Deployed cab962e with MkDocs version: 1.6.1
2026-04-26 Deployed 21650d8 with MkDocs version: 1.6.1
2026-04-26 Deployed be5d99c with MkDocs version: 1.6.1
2026-04-26 Deployed ac8f356 with MkDocs version: 1.6.1
2026-04-27 Deployed faf44b7 with MkDocs version: 1.6.1
2026-04-27 Deployed d5a4319 with MkDocs version: 1.6.1
2026-04-27 Deployed 5ca8a59 with MkDocs version: 1.6.1
2026-04-27 Deployed 290a8c8 with MkDocs version: 1.6.1
2026-04-27 Deployed fa20efc with MkDocs version: 1.6.1
2026-04-28 Deployed 8868f13 with MkDocs version: 1.6.1
2026-04-29 Deployed eb6e5c2 with MkDocs version: 1.6.1
2026-04-29 Deployed 31d115f with MkDocs version: 1.6.1
2026-04-29 exported some proper models with correct screen placing
2026-04-29 Deployed 58a826f with MkDocs version: 1.6.1
2026-04-29 Deployed 3ffe156 with MkDocs version: 1.6.1
2026-04-29 Deployed a3322cc with MkDocs version: 1.6.1
2026-04-29 added the solar assembly
2026-04-29 Deployed eecb59c with MkDocs version: 1.6.1
2026-04-30 exported the lastes baatch
2026-04-30 Deployed 8572a37 with MkDocs version: 1.6.1
2026-05-01 fix the screen inlay sizing for vs waveshared
2026-05-01 Deployed 22ed9a3 with MkDocs version: 1.6.1
2026-05-01 Deployed 605aa78 with MkDocs version: 1.6.1
2026-05-01 Deployed a69093b with MkDocs version: 1.6.1
2026-05-01 Deployed 1a0544d with MkDocs version: 1.6.1
2026-05-01 Deployed 09670d7 with MkDocs version: 1.6.1
2026-05-01 Deployed 96a6325 with MkDocs version: 1.6.1
2026-05-01 Deployed 29332bf with MkDocs version: 1.6.1
2026-05-01 Deployed bcbe3ee with MkDocs version: 1.6.1
2026-05-01 Deployed 5229edf with MkDocs version: 1.6.1
2026-05-01 Deployed 676c1a9 with MkDocs version: 1.6.1
2026-05-01 Deployed bbe932e with MkDocs version: 1.6.1
2026-05-01 Deployed 623e547 with MkDocs version: 1.6.1
2026-05-01 made latest printouts
2026-05-01 wiring
2026-05-01 Deployed eaea1c8 with MkDocs version: 1.6.1
2026-05-02 Deployed 5f57c60 with MkDocs version: 1.6.1
2026-05-02 Deployed 86191ed with MkDocs version: 1.6.1
2026-05-04 Deployed e11ba55 with MkDocs version: 1.6.1
2026-05-04 Deployed db96286 with MkDocs version: 1.6.1
2026-05-05 Deployed f57f2fb with MkDocs version: 1.6.1
2026-05-05 Deployed b97be53 with MkDocs version: 1.6.1
2026-05-05 Deployed a9876aa with MkDocs version: 1.6.1
2026-05-07 add init kicad files
